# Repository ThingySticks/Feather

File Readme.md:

# Feather Prototyping PCBs

Prototype board for Feather based devices (Adafruit Feather / Particle Mesh devices).

See individual versions for PCB specifics.

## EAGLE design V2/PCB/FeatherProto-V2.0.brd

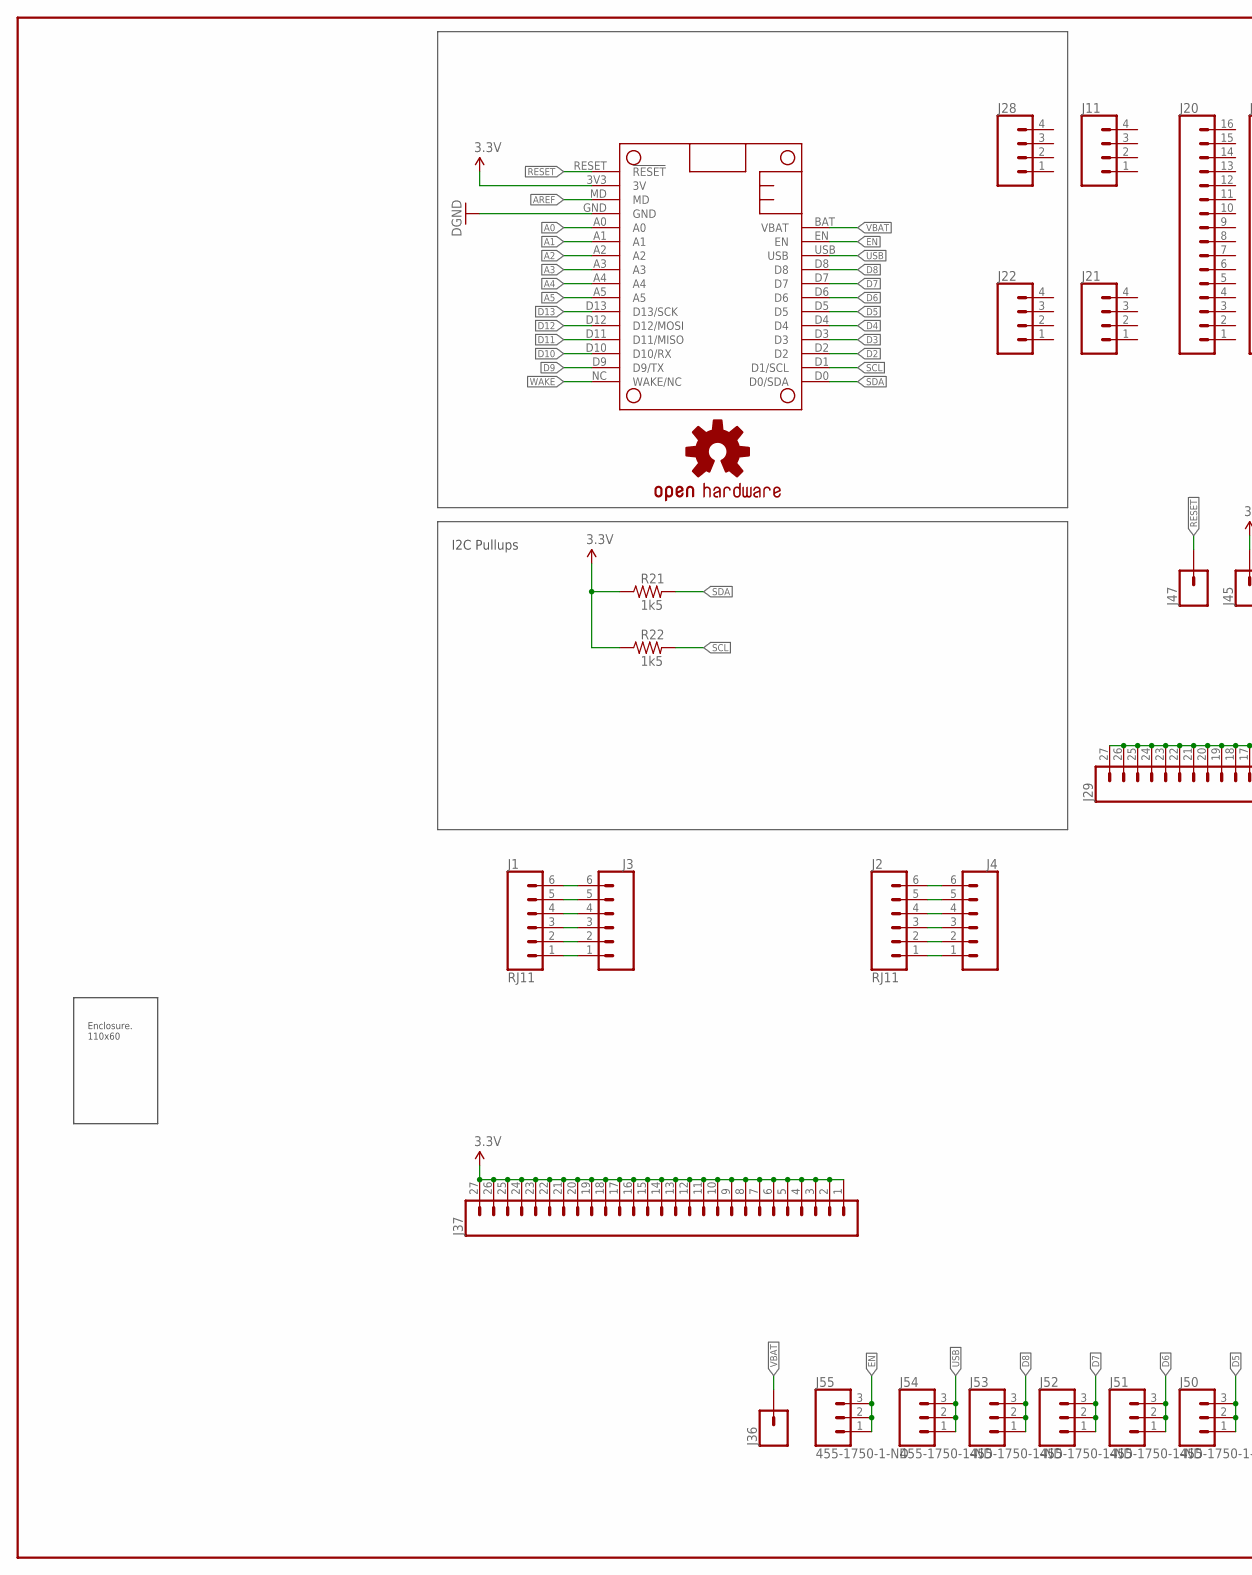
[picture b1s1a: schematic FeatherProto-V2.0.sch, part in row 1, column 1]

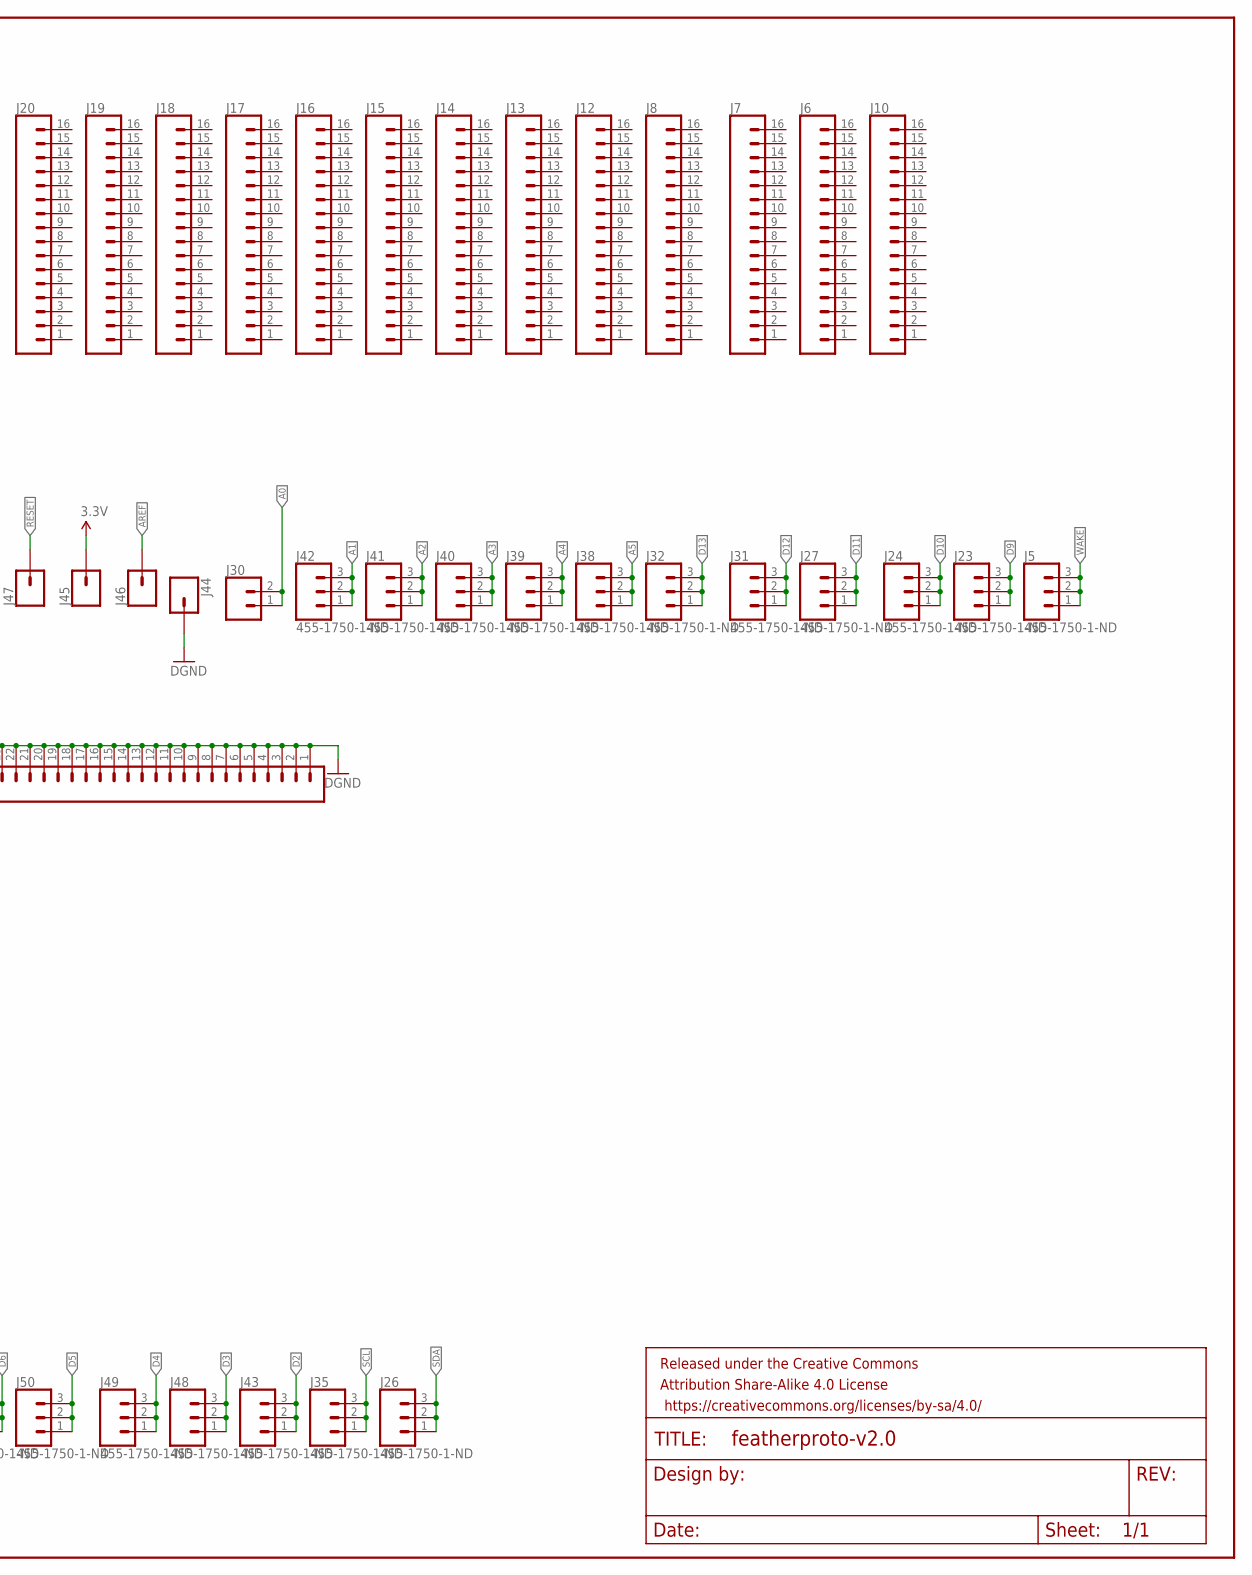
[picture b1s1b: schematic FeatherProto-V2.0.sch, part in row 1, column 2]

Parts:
FRAME2: FRAME-LEDGER; CREATIVE_COMMONS
J1, J2: RJ11; RJ11-6
J3, J4: CONN_06SILK_FEMALE_PTH; 1X06
J5, J23, J24, J26, J27, J31, J32, J35, J38, J39, J40, J41, J42, J43, J48, J49, J50, J51, J52, J53, J54, J55: 455-1750-1-ND; 1X03
J6, J7, J8, J10, J12, J13, J14, J15, J16, J17, J18, J19, J20: CONN_161X16_NO_SILK; 1X16_NO_SILK
J11, J21, J22, J28: CONN_041X04_NO_SILK; 1X04_NO_SILK
J29, J37: CONN_27; 1X27
J30: CONN_02; 1X02
J36, J44, J45, J46, J47: CONN_01PTH_NO_SILK_YES_STOP; 1X01_NO_SILK
LOGO1: OSHW-LOGOM; OSHW-LOGO-M
MS1: XENONA; XENON_BREAKOUT_A
R21, R22: 1k5; 0805
U$1: CAMDENBOSS-ENCLOSURE-110X60BOTH-EXTENDED-WIDE; CAMDENBOSS_ENCLOSURE_110X60_WIDE_EXTENDED

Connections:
3.3V: J37.1, J37.2, J37.3, J37.4, J37.5, J37.6, J37.7, J37.8, J37.9, J37.10, J37.11, J37.12, J37.13, J37.14, J37.15, J37.16, J37.17, J37.18, J37.19, J37.20, J37.21, J37.22, J37.23, J37.24, J37.25, J37.26, J37.27, J45.1, MS1.3V3 (3V), R21.1, R22.1
A0: J30.1, J30.2, MS1.A0
A1: J42.1, J42.2, J42.3, MS1.A1
A2: J41.1, J41.2, J41.3, MS1.A2
A3: J40.1, J40.2, J40.3, MS1.A3
A4: J39.1, J39.2, J39.3, MS1.A4
A5: J38.1, J38.2, J38.3, MS1.A5
AREF: J46.1, MS1.MD
D2: J43.1, J43.2, J43.3, MS1.D2
D3: J48.1, J48.2, J48.3, MS1.D3
D4: J49.1, J49.2, J49.3, MS1.D4
D5: J50.1, J50.2, J50.3, MS1.D5
D6: J51.1, J51.2, J51.3, MS1.D6
D7: J52.1, J52.2, J52.3, MS1.D7
D8: J53.1, J53.2, J53.3, MS1.D8
D9: J23.1, J23.2, J23.3, MS1.D9 (D9/TX)
D10: J24.1, J24.2, J24.3, MS1.D10 (D10/RX)
D11: J27.1, J27.2, J27.3, MS1.D11 (D11/MISO)
D12: J31.1, J31.2, J31.3, MS1.D12 (D12/MOSI)
D13: J32.1, J32.2, J32.3, MS1.D13 (D13/SCK)
EN: J55.1, J55.2, J55.3, MS1.EN
GND: J29.1, J29.2, J29.3, J29.4, J29.5, J29.6, J29.7, J29.8, J29.9, J29.10, J29.11, J29.12, J29.13, J29.14, J29.15, J29.16, J29.17, J29.18, J29.19, J29.20, J29.21, J29.22, J29.23, J29.24, J29.25, J29.26, J29.27, J44.1, MS1.GND
unnamed: J1.6, J3.6
unnamed: J1.5, J3.5
unnamed: J1.4, J3.4
unnamed: J1.3, J3.3
unnamed: J1.2, J3.2
unnamed: J1.1, J3.1
unnamed: J2.1, J4.1
unnamed: J2.2, J4.2
unnamed: J2.3, J4.3
unnamed: J2.4, J4.4
unnamed: J2.5, J4.5
unnamed: J2.6, J4.6
RESET: J47.1, MS1.RESET (!RESET)
SCL: J35.1, J35.2, J35.3, MS1.D1 (D1/SCL), R22.2
SDA: J26.1, J26.2, J26.3, MS1.D0 (D0/SDA), R21.2
USB: J54.1, J54.2, J54.3, MS1.USB
VBAT: J36.1, MS1.BAT (VBAT)
WAKE: J5.1, J5.2, J5.3, MS1.NC (WAKE/NC)

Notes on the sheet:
I2C Pullups

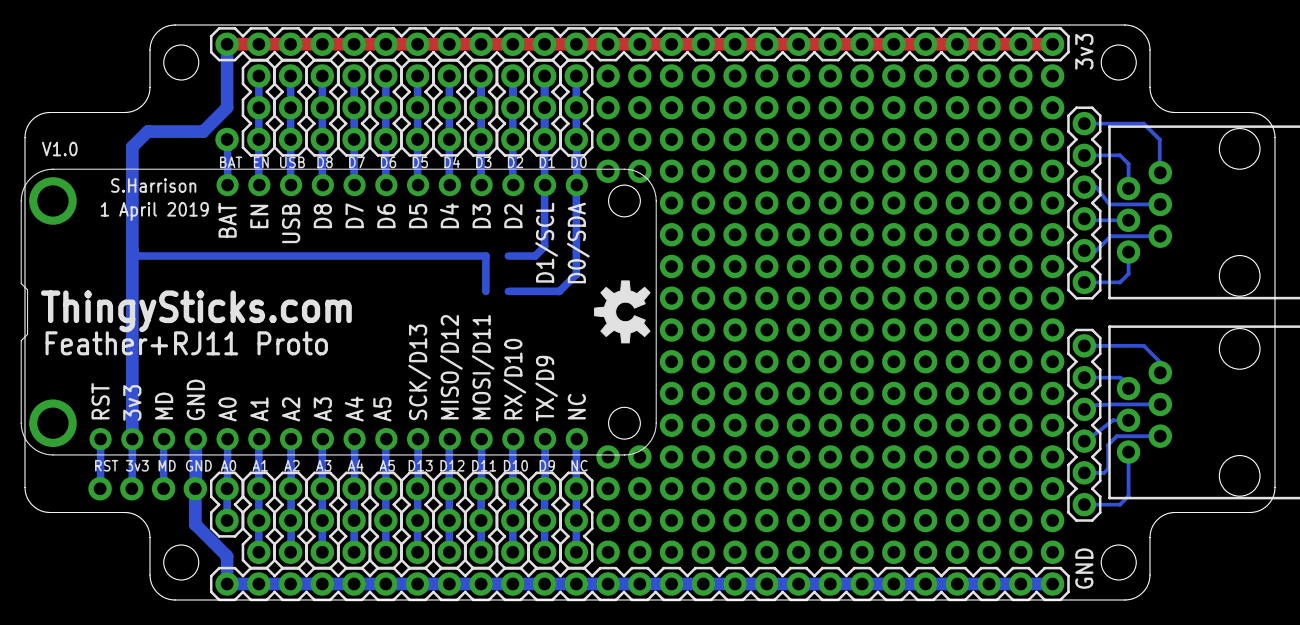
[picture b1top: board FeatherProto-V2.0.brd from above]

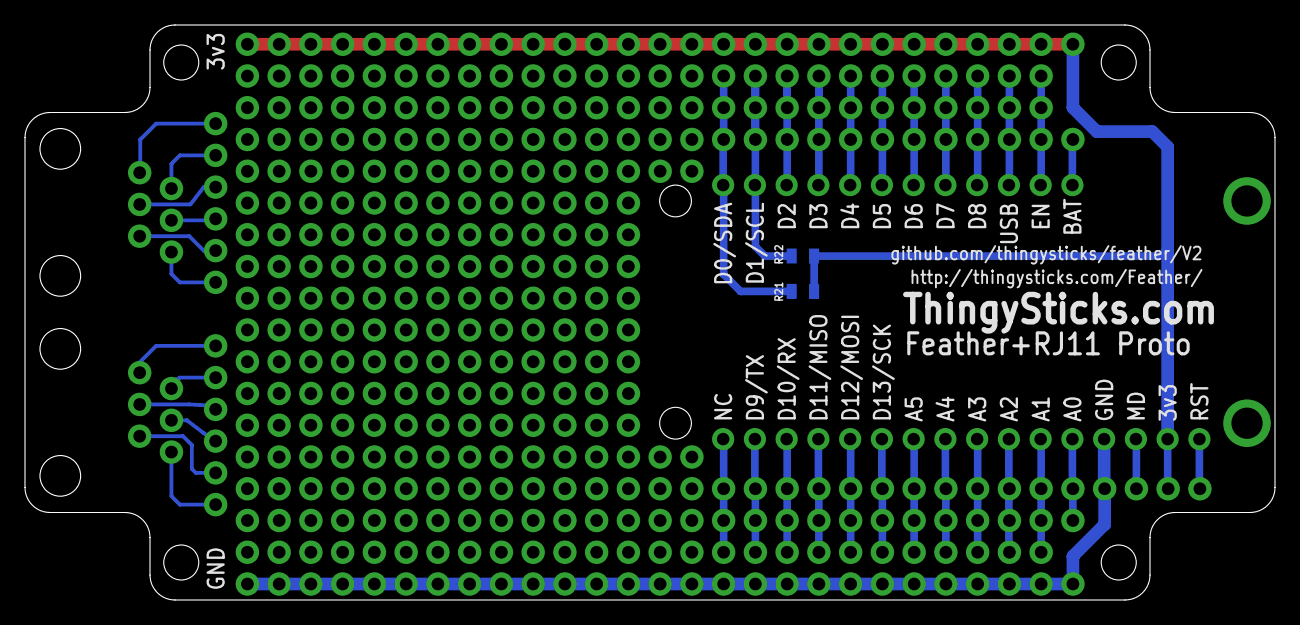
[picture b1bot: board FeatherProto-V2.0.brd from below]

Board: 2 copper layers, 100.0 x 46.0 mm, 57 parts (2 on the bottom side), 40 nets.

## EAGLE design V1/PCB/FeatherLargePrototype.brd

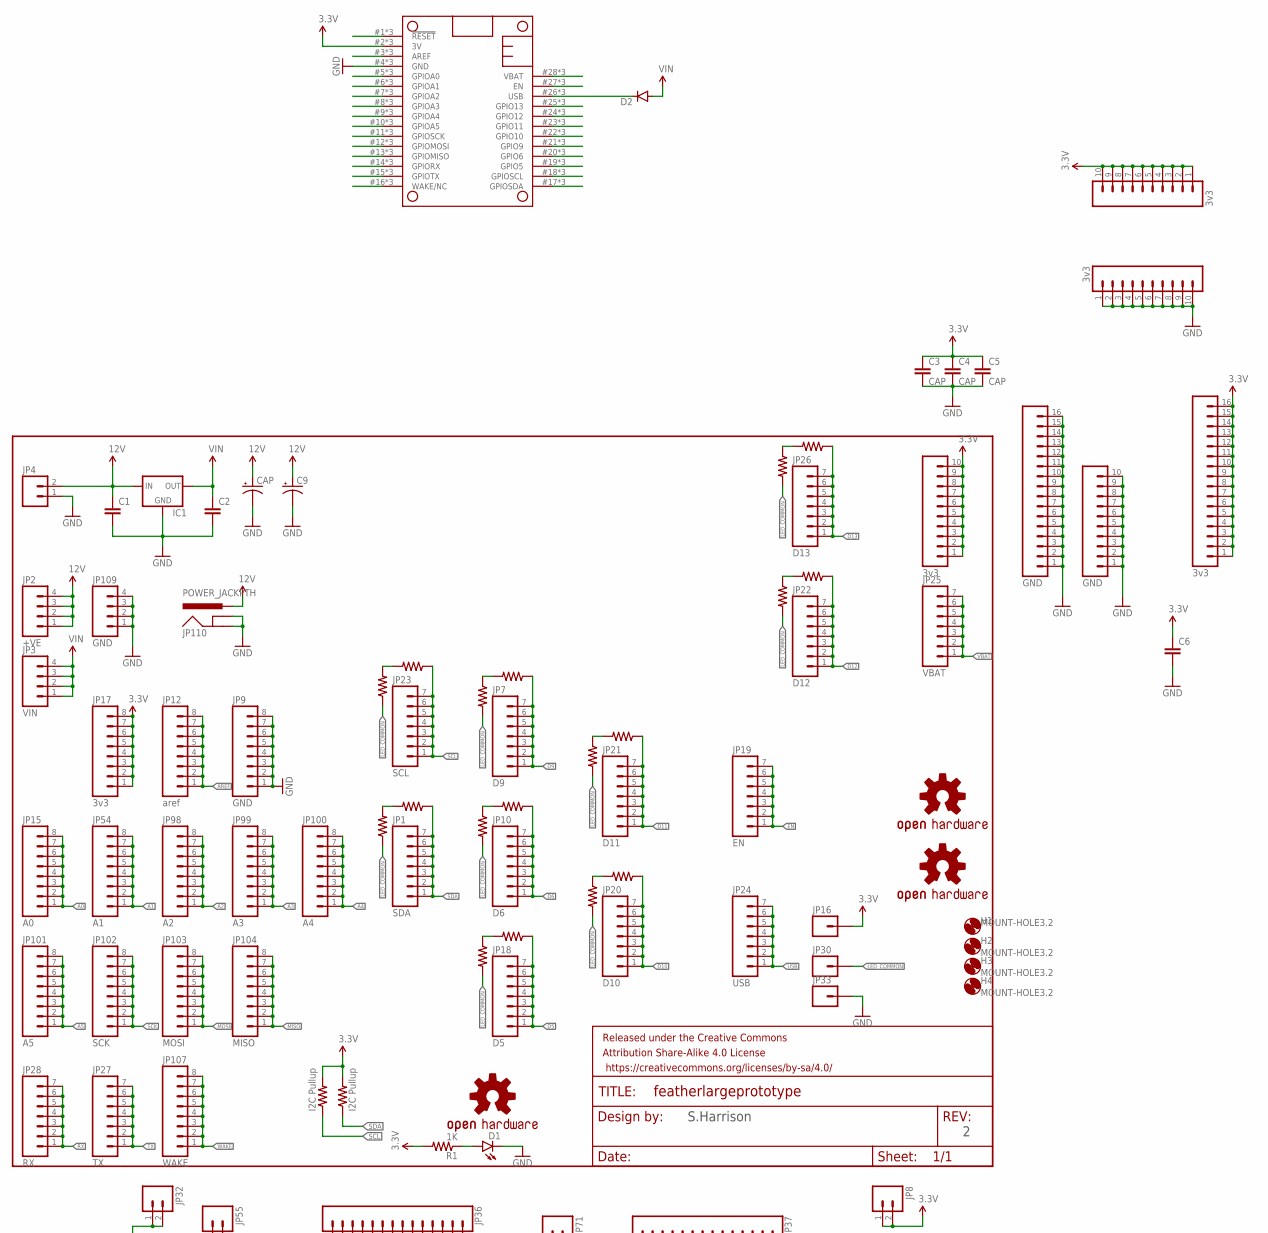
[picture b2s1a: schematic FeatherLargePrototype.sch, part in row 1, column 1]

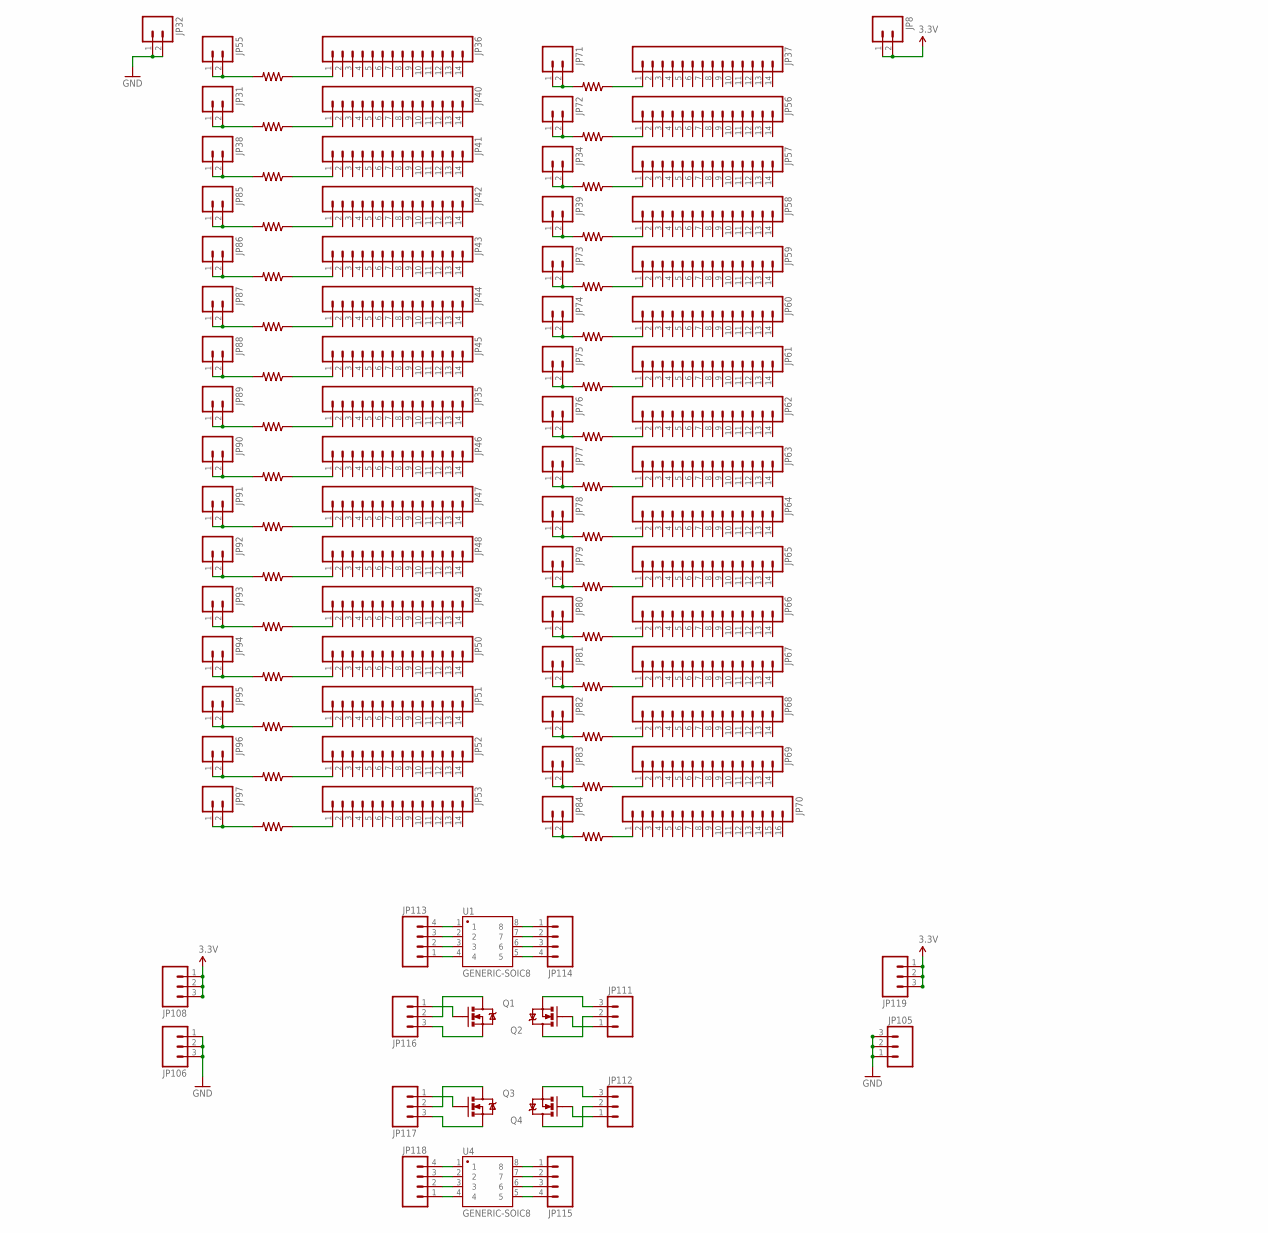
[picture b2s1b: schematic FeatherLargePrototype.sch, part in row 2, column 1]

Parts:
C1, C2, C6: CAP1206; 1206
C3, C4, C5: CAP; 1206
C9: CAP_POL7343; EIA7343
CAP: CAP_POLPTH1; CPOL-RADIAL-100UF-25V
D1: LED1206-BOTTOM; LED-1206-BOTTOM
D2: DIODESMA-ALT; SMA-DIODE_ALT
FRAME1: FRAME-LETTER; CREATIVE_COMMONS
H1, H2, H3, H4: MOUNT-HOLE3.2; 3,2
IC1: 78XXS
JP1: SDA; 1X07
JP2: +VE; 1X04
JP3: VIN; 1X04
JP4: M025MM; SCREWTERMINAL-5MM-2
JP5, JP6, JP29: 3v3; 1X10
JP7: D9; 1X07
JP8, JP31, JP32, JP34, JP38, JP39, JP55, JP71, JP72, JP73, JP74, JP75, JP76, JP77, JP78, JP79, JP80, JP81, JP82, JP83, JP84, JP85, JP86, JP87, JP88, JP89, JP90, JP91, JP92, JP93, JP94, JP95, JP96, JP97: M02PTH; 1X02
JP9: GND; 1X08_ROUND
JP10: D6; 1X07
JP11: GND; 1X10
JP12: aref; 1X08_ROUND
JP13: 3v3; 1X16
JP14: GND; 1X16
JP15: A0; 1X08_ROUND
JP16, JP30, JP33: M01PTH; 1X01
JP17: 3v3; 1X08_ROUND
JP18: D5; 1X07
JP19: EN; 1X07
JP20: D10; 1X07
JP21: D11; 1X07
JP22: D12; 1X07
JP23: SCL; 1X07
JP24: USB; 1X07
JP25: VBAT; 1X07
JP26: D13; 1X07
JP27: TX; 1X07
JP28: RX; 1X07
JP35, JP36, JP37, JP40, JP41, JP42, JP43, JP44, JP45, JP46, JP47, JP48, JP49, JP50, JP51, JP52, JP56, JP57, JP58, JP59, JP60, JP61, JP62, JP63, JP64, JP65, JP66, JP67, JP68, JP69: CONN_14CONNECTED; 1X14_CONNECTED
JP53: CONN_14NO_SILK; 1X14_NO_SILK
JP54: A1; 1X08_ROUND
JP70: M161X16_NO_SILK; 1X16_NO_SILK
JP98: A2; 1X08_ROUND
JP99: A3; 1X08_ROUND
JP100: A4; 1X08_ROUND
JP101: A5; 1X08_ROUND
JP102: SCK; 1X08_ROUND
JP103: MOSI; 1X08_ROUND
JP104: MISO; 1X08_ROUND
JP105, JP106, JP108, JP111, JP112, JP116, JP117, JP119: M03PTH; 1X03
JP107: WAKE; 1X08_ROUND
JP109: GND; 1X04
JP110: POWER_JACKPTH; POWER_JACK_PTH
JP113, JP114, JP115, JP118: M04NO_SILK_ALL_ROUND; 1X04_NO_SILK_ALL_ROUND
LOGO1, LOGO2: OSHW-LOGOL; OSHW-LOGO-L
LOGO3: OSHW-LOGOM; OSHW-LOGO-M
MS2: FEATHERWINGFEATHEWING_BREAKOUT; FEATHERWING_BREAKOUT
Q1, Q2, Q3, Q4: MOSFET-NCHANNELBSS123LT1G; SOT23-3
R1: 1K; 1206
R10, R11, R12, R13, R14, R15, R16, R17, R18, R19, R20, R21, R22, R23, R24, R25, R26, R27, R30, R31, R32, R33, R34, R35, R36, R37, R38, R39, R40, R41, R42, R43, R44, R45, R46, R47, R48, R49, R50, R51, R52, R53, R54, R55, R56, R57, R58, R59, R60, R61: RESISTOR1206; 1206
R62, R63: I2C Pullup; 1206
U1, U4: GENERIC-SOIC8; SO08-UNIVERSAL

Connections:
3.3V: C3.1, C4.1, C5.1, C6.1, JP5.1, JP5.2, JP5.3, JP5.4, JP5.5, JP5.6, JP5.7, JP5.8, JP5.9, JP5.10, JP6.1, JP6.2, JP6.3, JP6.4, JP6.5, JP6.6, JP6.7, JP6.8, JP6.9, JP6.10, JP8.1, JP8.2, JP13.1, JP13.2, JP13.3, JP13.4, JP13.5, JP13.6, JP13.7, JP13.8, JP13.9, JP13.10, JP13.11, JP13.12, JP13.13, JP13.14, JP13.15, JP13.16, JP16.1, JP17.1, JP17.2, JP17.3, JP17.4, JP17.5, JP17.6, JP17.7, JP17.8, JP108.1, JP108.2, JP108.3, JP119.1, JP119.2, JP119.3, MS2.2 (3V), MS2.#2 (3V), MS2.@2 (3V), R1.2, R62.2, R63.2
12V: C1.1, C9.A (+), CAP.1 (+), IC1.IN, JP2.1, JP2.2, JP2.3, JP2.4, JP4.2, JP110.PWR
A0: JP15.1, JP15.2, JP15.3, JP15.4, JP15.5, JP15.6, JP15.7, JP15.8, MS2.5 (GPIOA0), MS2.#5 (GPIOA0), MS2.@5 (GPIOA0)
A1: JP54.1, JP54.2, JP54.3, JP54.4, JP54.5, JP54.6, JP54.7, JP54.8, MS2.6 (GPIOA1), MS2.#6 (GPIOA1), MS2.@6 (GPIOA1)
A2: JP98.1, JP98.2, JP98.3, JP98.4, JP98.5, JP98.6, JP98.7, JP98.8, MS2.7 (GPIOA2), MS2.#7 (GPIOA2), MS2.@7 (GPIOA2)
A3: JP99.1, JP99.2, JP99.3, JP99.4, JP99.5, JP99.6, JP99.7, JP99.8, MS2.8 (GPIOA3), MS2.#8 (GPIOA3), MS2.@8 (GPIOA3)
A4: JP100.1, JP100.2, JP100.3, JP100.4, JP100.5, JP100.6, JP100.7, JP100.8, MS2.9 (GPIOA4), MS2.#9 (GPIOA4), MS2.@9 (GPIOA4)
A5: JP101.1, JP101.2, JP101.3, JP101.4, JP101.5, JP101.6, JP101.7, JP101.8, MS2.10 (GPIOA5), MS2.#10 (GPIOA5), MS2.@10 (GPIOA5)
AREF: JP12.1, JP12.2, JP12.3, JP12.4, JP12.5, JP12.6, JP12.7, JP12.8, MS2.3 (AREF), MS2.#3 (AREF), MS2.@3 (AREF)
D5: JP18.1, JP18.2, JP18.3, JP18.4, JP18.5, JP18.6, JP18.7, MS2.19 (GPIO5), MS2.#19 (GPIO5), MS2.@19 (GPIO5), R22.1
D6: JP10.1, JP10.2, JP10.3, JP10.4, JP10.5, JP10.6, JP10.7, MS2.20 (GPIO6), MS2.#20 (GPIO6), MS2.@20 (GPIO6), R20.1
D9: JP7.1, JP7.2, JP7.3, JP7.4, JP7.5, JP7.6, JP7.7, MS2.21 (GPIO9), MS2.#21 (GPIO9), MS2.@21 (GPIO9), R18.1
D10: JP20.1, JP20.2, JP20.3, JP20.4, JP20.5, JP20.6, JP20.7, MS2.22 (GPIO10), MS2.#22 (GPIO10), MS2.@22 (GPIO10), R16.1
D11: JP21.1, JP21.2, JP21.3, JP21.4, JP21.5, JP21.6, JP21.7, MS2.23 (GPIO11), MS2.#23 (GPIO11), MS2.@23 (GPIO11), R14.1
D12: JP22.1, JP22.2, JP22.3, JP22.4, JP22.5, JP22.6, JP22.7, MS2.24 (GPIO12), MS2.#24 (GPIO12), MS2.@24 (GPIO12), R12.1
D13: JP26.1, JP26.2, JP26.3, JP26.4, JP26.5, JP26.6, JP26.7, MS2.25 (GPIO13), MS2.#25 (GPIO13), MS2.@25 (GPIO13), R10.1
EN: JP19.1, JP19.2, JP19.3, JP19.4, JP19.5, JP19.6, JP19.7, MS2.27 (EN), MS2.#27 (EN), MS2.@27 (EN)
GND: C1.2, C2.2, C3.2, C4.2, C5.2, C6.2, C9.C (-), CAP.2 (-), D1.C, IC1.GND, JP4.1, JP9.1, JP9.2, JP9.3, JP9.4, JP9.5, JP9.6, JP9.7, JP9.8, JP11.1, JP11.2, JP11.3, JP11.4, JP11.5, JP11.6, JP11.7, JP11.8, JP11.9, JP11.10, JP14.1, JP14.2, JP14.3, JP14.4, JP14.5, JP14.6, JP14.7, JP14.8, JP14.9, JP14.10, JP14.11, JP14.12, JP14.13, JP14.14, JP14.15, JP14.16, JP29.1, JP29.2, JP29.3, JP29.4, JP29.5, JP29.6, JP29.7, JP29.8, JP29.9, JP29.10, JP32.1, JP32.2, JP33.1, JP105.1, JP105.2, JP105.3, JP106.1, JP106.2, JP106.3, JP109.1, JP109.2, JP109.3, JP109.4, JP110.GND, JP110.GNDBREAK, MS2.4 (GND), MS2.#4 (GND), MS2.@4 (GND)
LED_COMMON: JP30.1, R11.2, R13.2, R15.2, R17.2, R19.2, R21.2, R23.2, R25.1, R27.1
MISO: JP104.1, JP104.2, JP104.3, JP104.4, JP104.5, JP104.6, JP104.7, JP104.8, MS2.13 (GPIOMISO), MS2.#13 (GPIOMISO), MS2.@13 (GPIOMISO)
MOSI: JP103.1, JP103.2, JP103.3, JP103.4, JP103.5, JP103.6, JP103.7, JP103.8, MS2.12 (GPIOMOSI), MS2.#12 (GPIOMOSI), MS2.@12 (GPIOMOSI)
unnamed: D1.A, R1.1
unnamed: JP113.4, U1.1
unnamed: JP113.3, U1.2
unnamed: R10.2, R11.1
unnamed: JP113.2, U1.3
unnamed: JP113.1, U1.4
unnamed: JP114.1, U1.8
unnamed: JP114.2, U1.7
unnamed: R12.2, R13.1
unnamed: R14.2, R15.1
unnamed: R16.2, R17.1
unnamed: JP114.3, U1.6
unnamed: JP114.4, U1.5
unnamed: JP112.3, Q4.2 (S)
unnamed: R18.2, R19.1
unnamed: JP116.2, Q1.3 (D)
unnamed: R20.2, R21.1
unnamed: JP116.1, Q1.1 (G)
unnamed: R22.2, R23.1
unnamed: JP71.1, JP71.2, R46.2
unnamed: JP116.3, Q1.2 (S)
unnamed: R26.2, R27.2
unnamed: R24.2, R25.2
unnamed: JP117.2, Q3.3 (D)
unnamed: JP72.1, JP72.2, R47.2
unnamed: JP34.1, JP34.2, R48.2
unnamed: JP39.1, JP39.2, R49.2
unnamed: JP73.1, JP73.2, R50.2
unnamed: JP74.1, JP74.2, R51.2
unnamed: JP75.1, JP75.2, R52.2
unnamed: JP76.1, JP76.2, R53.2
unnamed: JP77.1, JP77.2, R54.2
unnamed: JP78.1, JP78.2, R55.2
unnamed: JP79.1, JP79.2, R56.2
unnamed: JP80.1, JP80.2, R57.2
unnamed: JP81.1, JP81.2, R58.2
unnamed: JP82.1, JP82.2, R59.2
unnamed: JP83.1, JP83.2, R60.2
unnamed: JP84.1, JP84.2, R61.2
unnamed: JP70.1, R61.1
unnamed: JP69.1, R60.1
unnamed: JP68.1, R59.1
unnamed: JP67.1, R58.1
unnamed: JP66.1, R57.1
unnamed: JP65.1, R56.1
unnamed: JP64.1, R55.1
unnamed: JP63.1, R54.1
unnamed: JP62.1, R53.1
unnamed: JP61.1, R52.1
unnamed: JP60.1, R51.1
unnamed: JP59.1, R50.1
unnamed: JP58.1, R49.1
unnamed: JP57.1, R48.1
unnamed: JP56.1, R47.1
unnamed: JP37.1, R46.1
unnamed: JP97.1, JP97.2, R45.2
unnamed: JP96.1, JP96.2, R44.2
unnamed: JP95.1, JP95.2, R43.2
unnamed: JP94.1, JP94.2, R42.2
unnamed: JP93.1, JP93.2, R41.2
unnamed: JP92.1, JP92.2, R40.2
unnamed: JP91.1, JP91.2, R39.2
unnamed: JP90.1, JP90.2, R38.2
unnamed: JP89.1, JP89.2, R37.2
unnamed: JP88.1, JP88.2, R36.2
unnamed: JP87.1, JP87.2, R35.2
unnamed: JP86.1, JP86.2, R34.2
unnamed: JP85.1, JP85.2, R33.2
unnamed: JP38.1, JP38.2, R32.2
unnamed: JP55.1, JP55.2, R30.2
unnamed: JP36.1, R30.1
unnamed: JP40.1, R31.1
unnamed: JP41.1, R32.1
unnamed: JP42.1, R33.1
unnamed: JP43.1, R34.1
unnamed: JP44.1, R35.1
unnamed: JP45.1, R36.1
unnamed: JP35.1, R37.1
unnamed: JP46.1, R38.1
unnamed: JP47.1, R39.1
unnamed: JP48.1, R40.1
unnamed: JP49.1, R41.1
unnamed: JP50.1, R42.1
unnamed: JP51.1, R43.1
unnamed: JP52.1, R44.1
unnamed: JP53.1, R45.1
unnamed: JP31.1, JP31.2, R31.2
unnamed: JP117.1, Q3.1 (G)
unnamed: JP117.3, Q3.2 (S)
unnamed: JP118.4, U4.1
unnamed: JP118.3, U4.2
unnamed: JP118.2, U4.3
unnamed: JP118.1, U4.4
unnamed: JP115.1, U4.8
unnamed: JP115.2, U4.7
unnamed: JP115.3, U4.6
unnamed: JP115.4, U4.5
unnamed: JP112.2, Q4.3 (D)
unnamed: JP112.1, Q4.1 (G)
unnamed: JP111.2, Q2.3 (D)
unnamed: JP111.1, Q2.1 (G)
unnamed: JP111.3, Q2.2 (S)
RESET: MS2.1 (!RESET), MS2.#1 (!RESET), MS2.@1 (!RESET)
RX: JP28.1, JP28.2, JP28.3, JP28.4, JP28.5, JP28.6, JP28.7, MS2.14 (GPIORX), MS2.#14 (GPIORX), MS2.@14 (GPIORX)
SCK: JP102.1, JP102.2, JP102.3, JP102.4, JP102.5, JP102.6, JP102.7, JP102.8, MS2.11 (GPIOSCK), MS2.#11 (GPIOSCK), MS2.@11 (GPIOSCK)
SCL: JP23.1, JP23.2, JP23.3, JP23.4, JP23.5, JP23.6, JP23.7, MS2.18 (GPIOSCL), MS2.#18 (GPIOSCL), MS2.@!8 (GPIOSCL), R24.1, R62.1
SDA: JP1.1, JP1.2, JP1.3, JP1.4, JP1.5, JP1.6, JP1.7, MS2.17 (GPIOSDA), MS2.#17 (GPIOSDA), MS2.@17 (GPIOSDA), R26.1, R63.1
TX: JP27.1, JP27.2, JP27.3, JP27.4, JP27.5, JP27.6, JP27.7, MS2.15 (GPIOTX), MS2.#15 (GPIOTX), MS2.@15 (GPIOTX)
USB: D2.C, JP24.1, JP24.2, JP24.3, JP24.4, JP24.5, JP24.6, JP24.7, MS2.26 (USB), MS2.#26 (USB), MS2.@26 (USB)
VBAT: JP25.1, JP25.2, JP25.3, JP25.4, JP25.5, JP25.6, JP25.7, MS2.28 (VBAT), MS2.#28 (VBAT), MS2.@28 (VBAT)
VIN: C2.1, D2.A, IC1.OUT, JP3.1, JP3.2, JP3.3, JP3.4
WAKE: JP107.1, JP107.2, JP107.3, JP107.4, JP107.5, JP107.6, JP107.7, JP107.8, MS2.16 (WAKE/NC), MS2.#16 (WAKE/NC), MS2.@16 (WAKE/NC)

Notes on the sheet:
S.Harrison

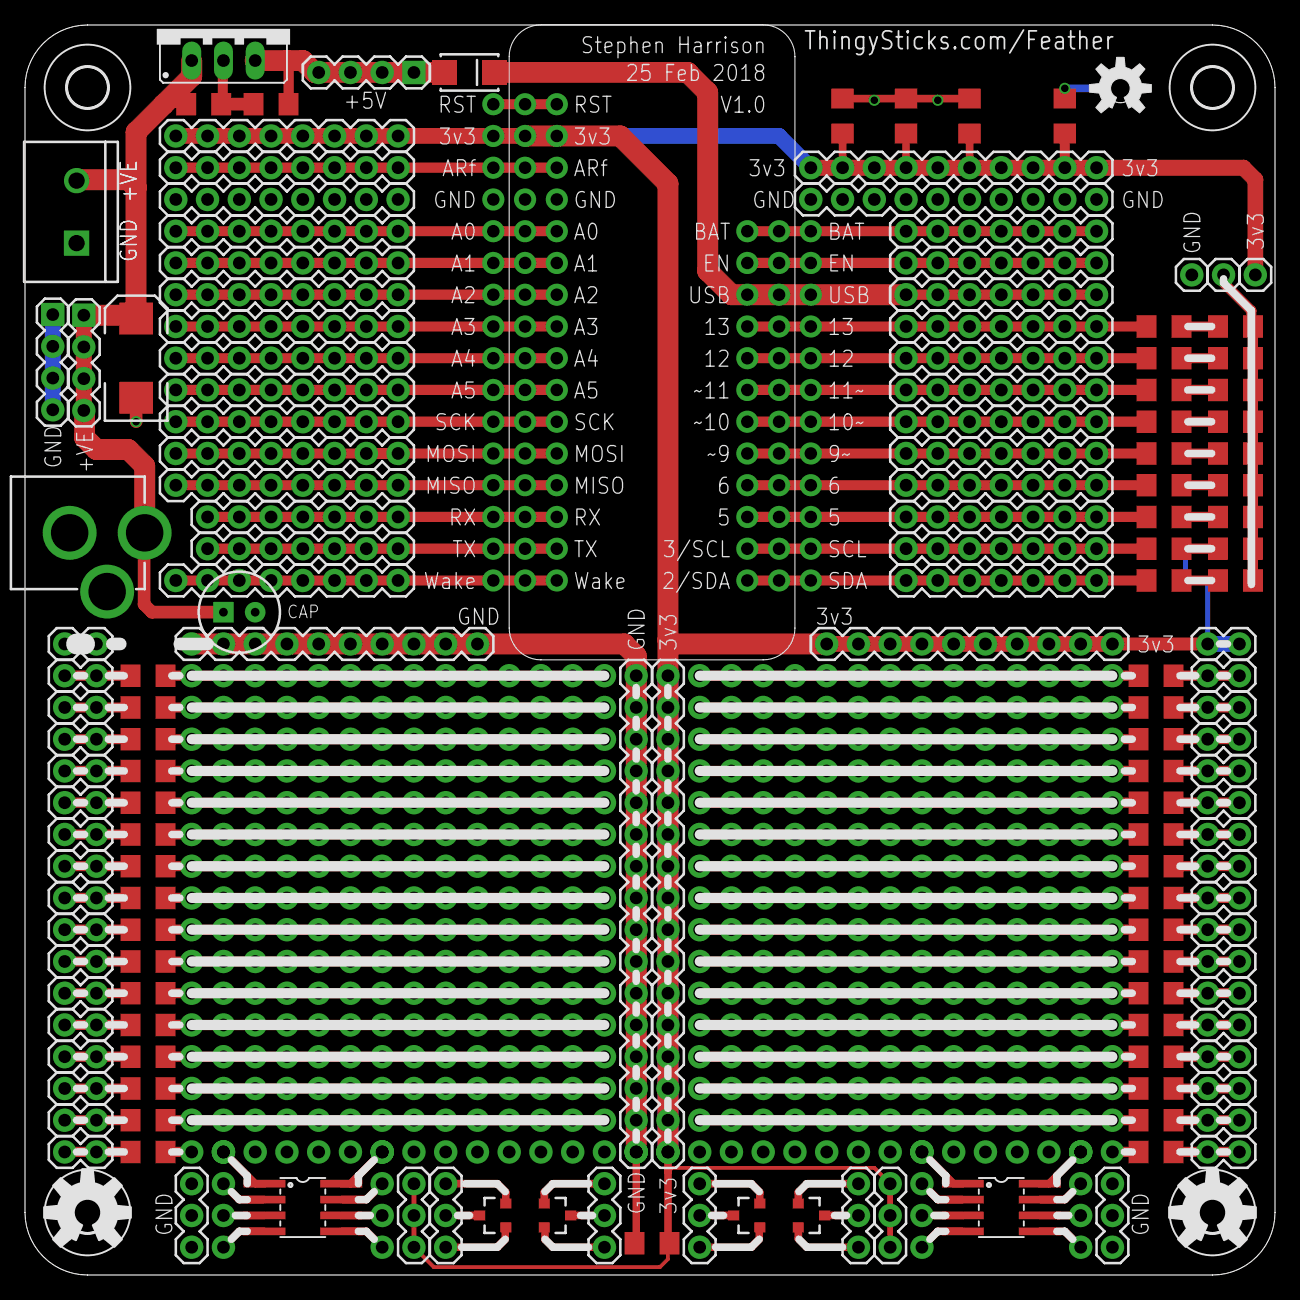
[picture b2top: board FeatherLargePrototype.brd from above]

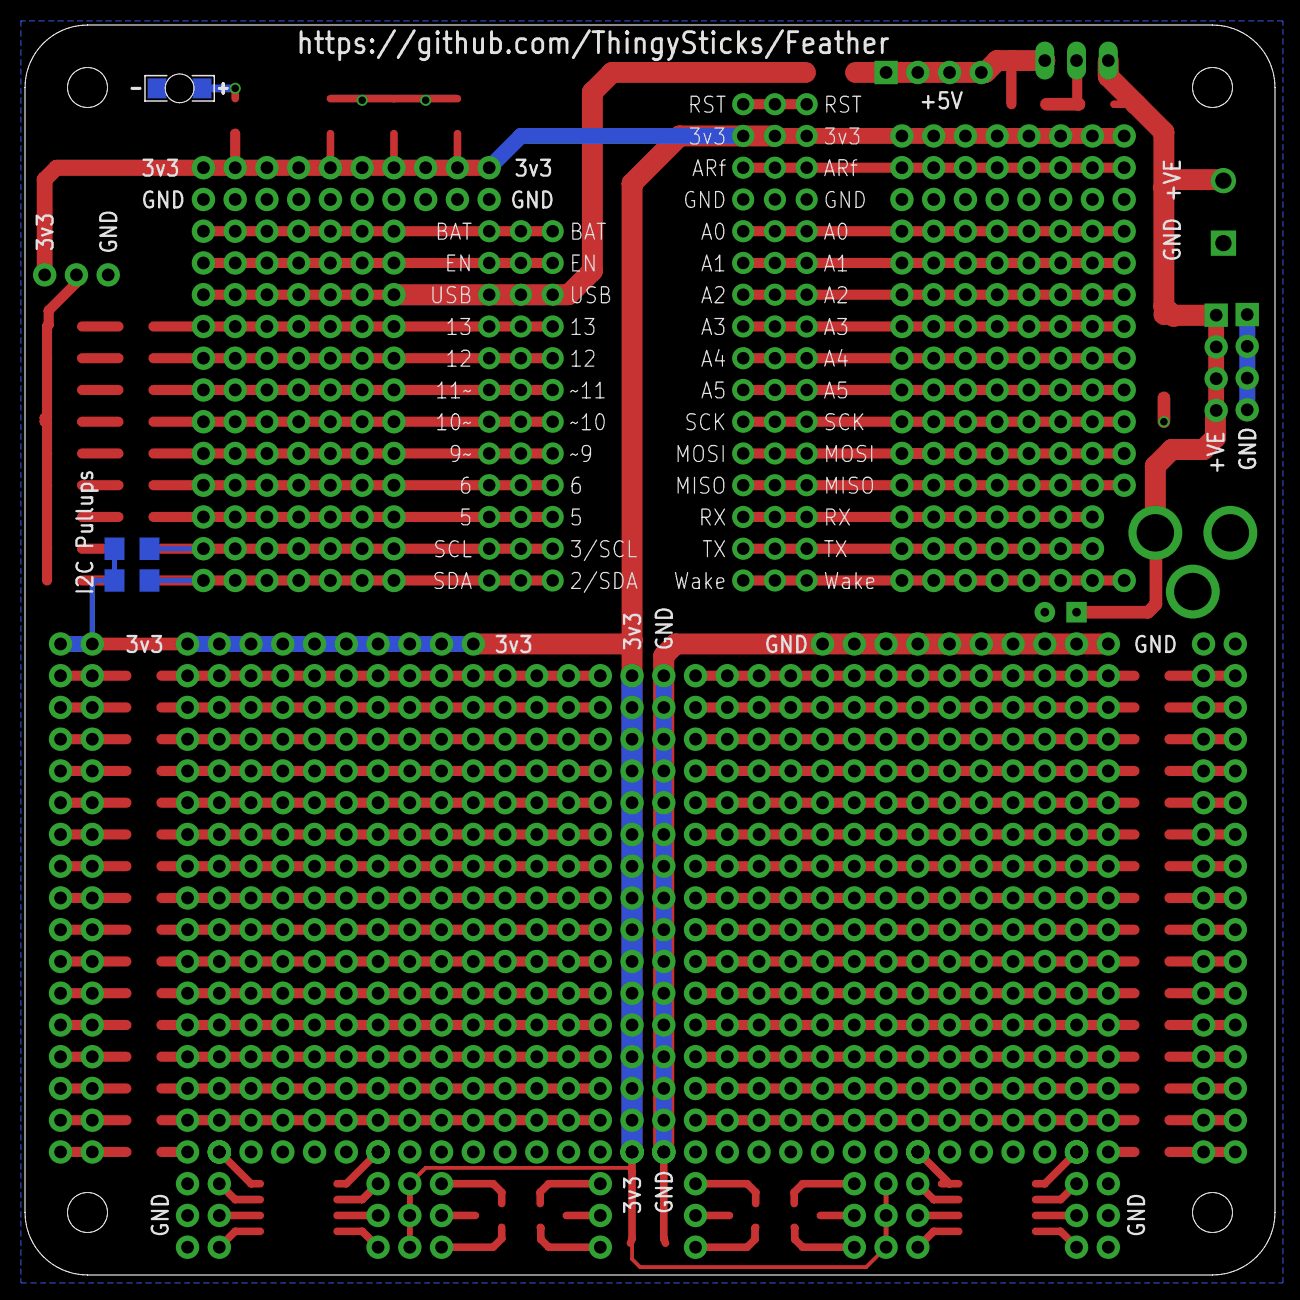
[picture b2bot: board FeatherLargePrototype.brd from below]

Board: 2 copper layers, 100.0 x 100.0 mm, 198 parts (3 on the bottom side), 133 nets.

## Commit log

2018-02-25 First version
2020-03-30 Added V4 PCB. Feather + RJ45 connectors.
2020-03-30 Adding V3 (simple feather prototype PCB)
2020-03-30 Added V2 RJ11 Feather proto

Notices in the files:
parts and their libraries:
SparkFun-Capacitors: Licensing: Creative Commons ShareAlike 4.0 International - https://creativecommons.org/licenses/by-sa/4.0
SparkFun-Aesthetics: Released under the Creative Commons Attribution Share-Alike 4.0 License
SparkFun-Aesthetics: https://creativecommons.org/licenses/by-sa/4.0
